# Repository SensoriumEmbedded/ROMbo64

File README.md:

# ROMbo64
 Replacement Kernal, Character, and BASIC ROMs in a single EEPROM
 I had a working proto and was finalizing logic when I came across this project: https://github.com/hbekel/reprom64
 Based on this, I addopted some of their design choices into mine, full credit goes to the REPROM64 project.  In fact, that project covers more C64/128 models, and is therefore a more thorough solution
 Mine is a bit more compact PCB, but will only work (without wires) with the 250407 and 250425 C64 PCA versions.  Other versions would have to extend the BASIC and Char ROM Cip Select lines to the ROMbo64 board.
 Rom selection can be done by jumpers, switched, or driven from a microcontroller such as Arduino.

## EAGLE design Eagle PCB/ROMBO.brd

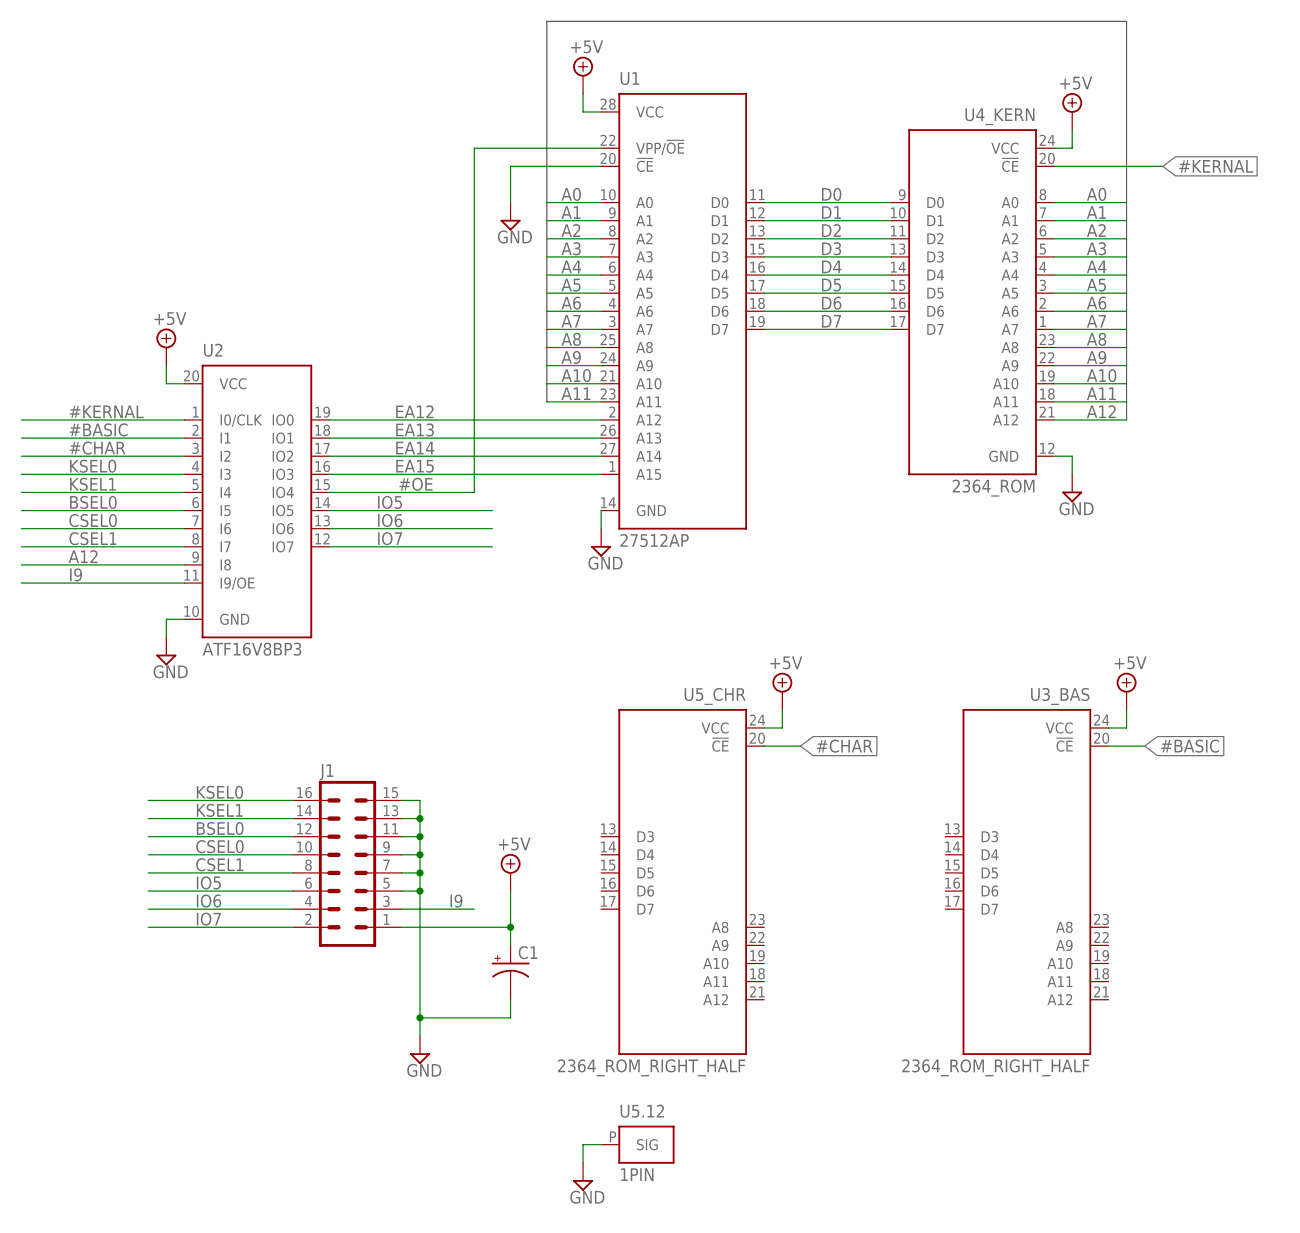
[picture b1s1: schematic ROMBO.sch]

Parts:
C1: CPOL-USE2.5-6; E2,5-6
J1: MA08-2
U1: 27512AP; DIL28-6
U2: ATF16V8BP3; DIL20
U3_BAS, U5_CHR: 2364_ROM_RIGHT_HALF; SIL12
U4_KERN: 2364_ROM; DIL24-6
U5.12: 1PIN

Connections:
#BASIC: U2.2 (I1), U3_BAS.20 (!CE)
#CHAR: U2.3 (I2), U5_CHR.20 (!CE)
#KERNAL: U2.1 (I0/CLK), U4_KERN.20 (!CE)
#OE: U1.22 (VPP/!OE), U2.15 (IO4)
+5V: C1.+, J1.1, U1.28 (VCC), U2.20 (VCC), U3_BAS.24 (VCC), U4_KERN.24 (VCC), U5_CHR.24 (VCC)
A0: U1.10 (A0), U4_KERN.8 (A0)
A1: U1.9 (A1), U4_KERN.7 (A1)
A2: U1.8 (A2), U4_KERN.6 (A2)
A3: U1.7 (A3), U4_KERN.5 (A3)
A4: U1.6 (A4), U4_KERN.4 (A4)
A5: U1.5 (A5), U4_KERN.3 (A5)
A6: U1.4 (A6), U4_KERN.2 (A6)
A7: U1.3 (A7), U4_KERN.1 (A7)
A8: U1.25 (A8), U4_KERN.23 (A8)
A9: U1.24 (A9), U4_KERN.22 (A9)
A10: U1.21 (A10), U4_KERN.19 (A10)
A11: U1.23 (A11), U4_KERN.18 (A11)
A12: U2.9 (I8), U4_KERN.21 (A12)
BSEL0: J1.12, U2.6 (I5)
CSEL0: J1.10, U2.7 (I6)
CSEL1: J1.8, U2.8 (I7)
D0: U1.11 (D0), U4_KERN.9 (D0)
D1: U1.12 (D1), U4_KERN.10 (D1)
D2: U1.13 (D2), U4_KERN.11 (D2)
D3: U1.15 (D3), U4_KERN.13 (D3)
D4: U1.16 (D4), U4_KERN.14 (D4)
D5: U1.17 (D5), U4_KERN.15 (D5)
D6: U1.18 (D6), U4_KERN.16 (D6)
D7: U1.19 (D7), U4_KERN.17 (D7)
EA12: U1.2 (A12), U2.19 (IO0)
EA13: U1.26 (A13), U2.18 (IO1)
EA14: U1.27 (A14), U2.17 (IO2)
EA15: U1.1 (A15), U2.16 (IO3)
GND: C1.-, J1.5, J1.7, J1.9, J1.11, J1.13, J1.15, U1.14 (GND), U1.20 (!CE), U2.10 (GND), U4_KERN.12 (GND), U5.12.P
I9: J1.3, U2.11 (I9/OE)
IO5: J1.6, U2.14 (IO5)
IO6: J1.4, U2.13 (IO6)
IO7: J1.2, U2.12 (IO7)
KSEL0: J1.16, U2.4 (I3)
KSEL1: J1.14, U2.5 (I4)

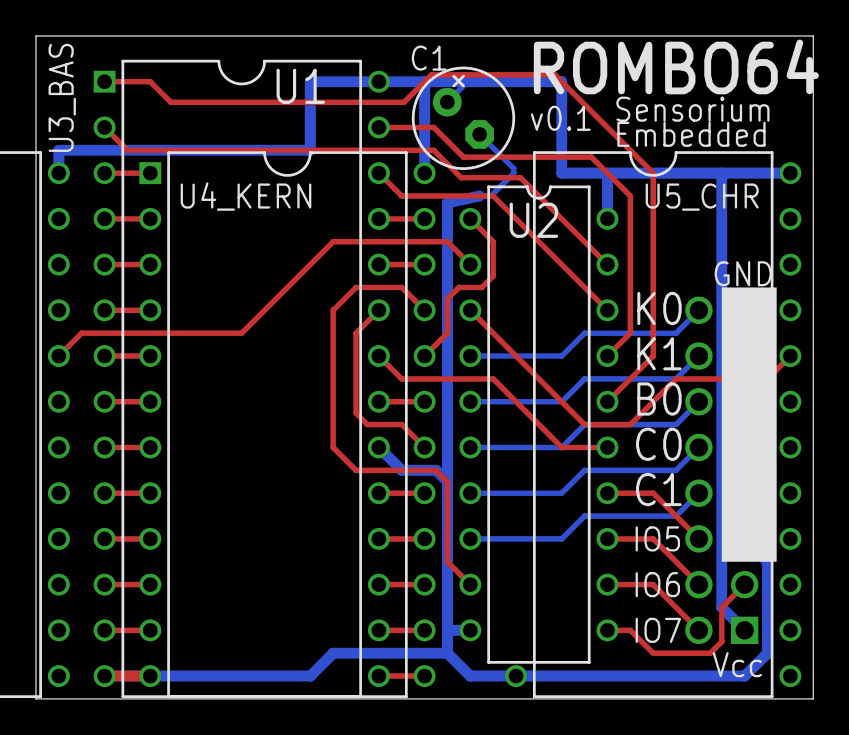
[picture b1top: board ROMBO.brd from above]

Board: 2 copper layers, 43.2 x 36.8 mm, 8 parts (0 on the bottom side), 40 nets.

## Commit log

2023-02-01 Initial check-in, PCB and GAL code
